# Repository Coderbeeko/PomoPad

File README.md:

# PomoPad
3x3 RP2040 macropad with encoder, OLED, and RGB. Built using QMK.

### How it started 

It all started when I saw a reel on instagram while mindlessly scrolling of course. It was someone spreading awareness of HC and Blueprint, and when I saw what it had to offer, I was immediately invested. 

I had never done a proper electronics project before, just a few simple Arduino projects, but besides that, I had never designed a PCB, used CAD properly, or dealt with firmware before, therefore this project really taught me so much new things, especially in a field that I want to purse long-term. My goal is to study Electrical and Electronics Engineering in university, and this project gave me a small, but truly exciting glimpse into that world.

Eventhough the macropad itself is relatively simple, the process widened my perspective and showed me how much there is to learn.

### Difficulties:

I wouldn't say that any one part was significantly easier than the others, because they all required a lot of time and focus, however firmware was probably the biggest challenge. 

I genuinely spend two days just trying to compile everything, especially when there were errors flooding my terminal everytime I tried to compile! Even fusion tested my patience, especially when adjusting precise hole dimensions or reworking the case design after ideas came up.

That said, those challenges made the project memorable and exciting. I still remember that second when the firmware finally compiled, definitely one of the most satisfying parts of the whole process.

### BOM:

- 6x Cherry MX Switches
- 6x SK6812 MINI-E LEDs
- 1x Seeed XIAO RP2040
- 7x Through-hole 1N4148 Diodes
- 1x EC11 Rotary encoder
- 1x 0.91" OLED display

### Schematic

### PCB

### Case without the PCB

### Top of the Case and Cover

### Top Layer

### Middle Layer

### Bottom Layer

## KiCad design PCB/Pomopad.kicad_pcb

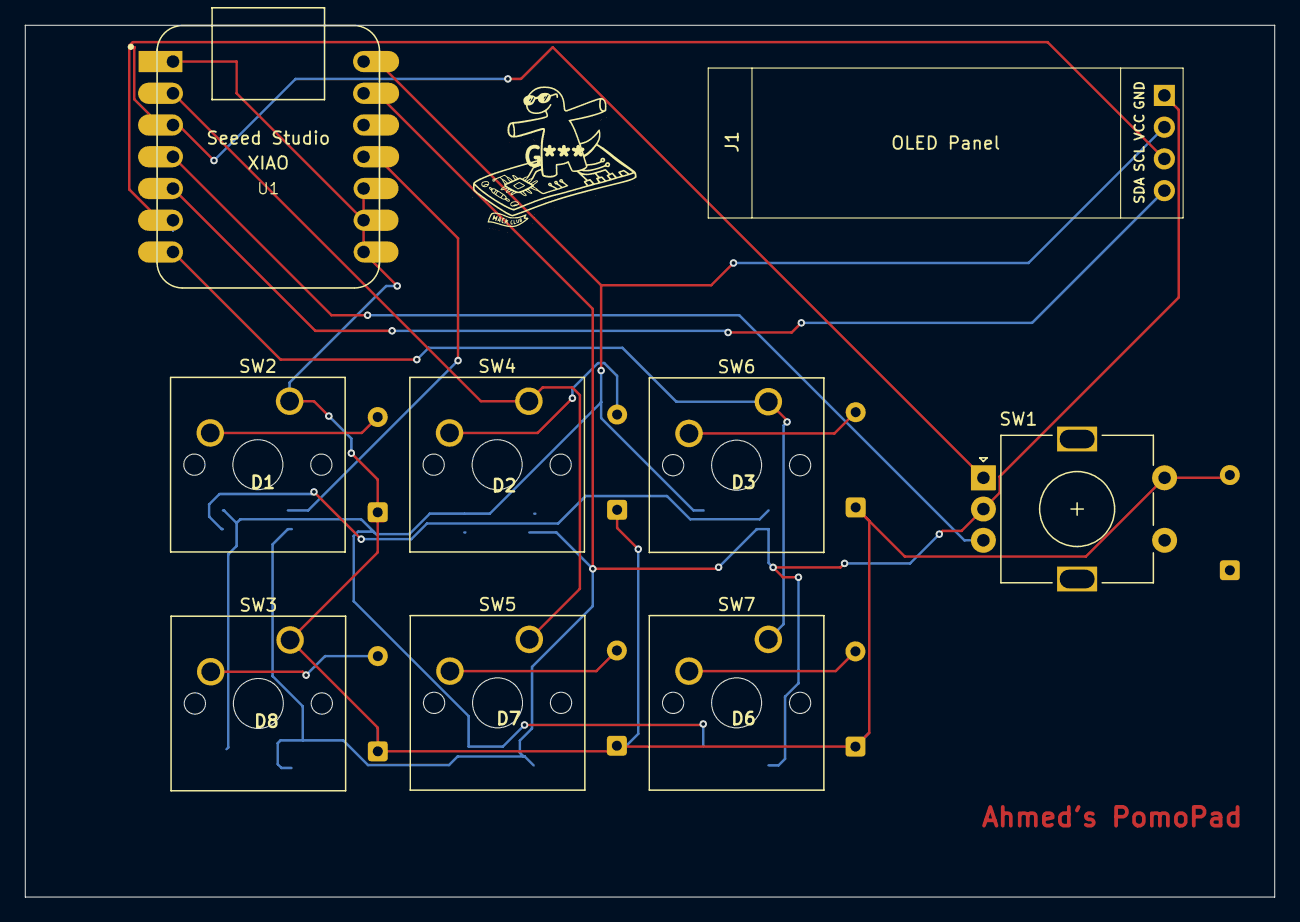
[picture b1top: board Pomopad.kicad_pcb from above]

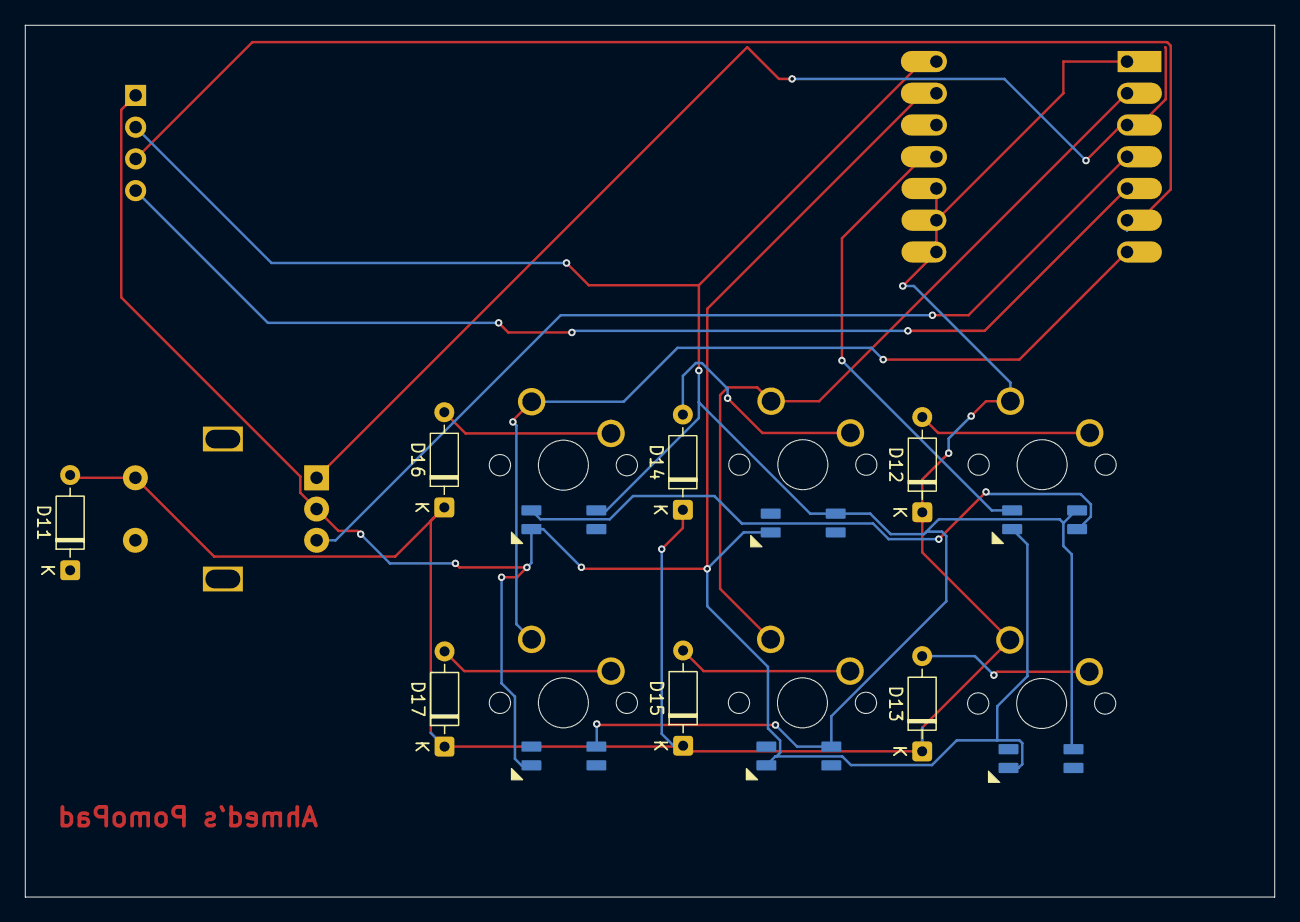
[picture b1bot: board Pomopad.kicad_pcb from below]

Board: 2 copper layers, 100.0 x 69.8 mm, 22 parts (7 on the bottom side), 17 nets.

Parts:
D1, D2, D3, D6, D7, D8: SK6812MINI-E; SK6812MINI-E_fixed
D11, D12, D13, D14, D15, D16, D17: 1N914; D_DO-35_SOD27_P7.62mm_Horizontal
J1: OLED; SSD1306-0.91-OLED-4pin-128x32
SW1: RotaryEncoder_Switch; RotaryEncoder_Alps_EC11E-Switch_Vertical_H20mm
SW2, SW3, SW4, SW5, SW6, SW7: SW_Push; SW_Cherry_MX_1.00u_PCB
U1: MOUDLE-SEEEDUINO-XIAO; XIAO-Generic-Hybrid-14P-2.54-21X17.8MM

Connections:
+5V: D1.1 (VDD), D2.1 (VDD), D3.1 (VDD), D6.1 (VDD), D7.1 (VDD), D8.1 (VDD), J1.2 (VCC), U1.14 (5V)
A: SW1.A, U1.3 (PA10_A2_D2)
B: SW1.B, U1.4 (PA11_A3_D3)
C0: D11.2 (A), D12.1 (K), D13.1 (K), D14.1 (K), D15.1 (K), D16.1 (K), D17.1 (K), SW1.S2, SW2.1, SW3.1, U1.1 (PA02_A0_D0), U1.8 (PB09_A7_D7_RX), U1.9 (PA7_A8_D8_SCK), U1.10 (PA5_A9_D9_MISO)
C1: SW4.1, SW5.1, U1.2 (PA4_A1_D1)
C2: SW6.1, SW7.1, U1.7 (PB08_A6_D6_TX)
GND: D1.3 (VSS), D2.3 (VSS), D3.3 (VSS), D6.3 (VSS), D7.3 (VSS), D8.3 (VSS), J1.1 (GND), SW1.C, U1.13 (GND)
LED: D1.4 (DIN), U1.11 (PA6_A10_D10_MOSI)
unnamed: D1.2 (DOUT), D3.4 (DIN)
unnamed: D12.2 (A), SW2.2
unnamed: D13.2 (A), SW3.2
unnamed: D14.2 (A), SW4.2
unnamed: D15.2 (A), SW5.2
unnamed: D16.2 (A), SW6.2
unnamed: D17.2 (A), SW7.2
SCL: J1.3 (SCl), U1.6 (PA9_A5_D5_SCL)
SDA: J1.4 (SDA), U1.5 (PA8_A4_D4_SDA)

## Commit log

2026-02-22 Update README.md with project description and BOM
2026-02-22 Add full project files (CAD, PCB, firmware, production)
2026-02-22 Final enclosure update + updated images
2026-02-26 Updated firmware: moved encoder push into matrix, set diode direction COL2ROW
